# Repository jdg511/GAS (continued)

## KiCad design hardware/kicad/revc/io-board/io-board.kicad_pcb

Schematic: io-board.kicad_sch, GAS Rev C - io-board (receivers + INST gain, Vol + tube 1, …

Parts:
C21, C22, C31, C32, C41, C42, C51, C52, C61, C62, C71, C81, C83, C85, C91, C92, C111, C112, C901, C902, C921, C922: 100nF; C_0603_1608Metric; MPN CL10B104KB8NNNC
C82, C93, C94, C8004, C8104: 10uF 25V; CP_Elec_5x5.8; MPN UWT1E100MCL1GB
C84: 47uF 16V; CP_Elec_6.3x7.7; MPN EEE-FK1C470P
C95: 10uF; C_0805_2012Metric; MPN CL21A106KAYNNNE
C101, C121, C201, C301, C601, C611, C4005, C4105, C7005, C7105: 22pF; C_0603_1608Metric; MPN CL10C220JB8NNNC
C4001, C4101, C7001, C7101: 22nF C0G; C_1206_3216Metric; MPN GRM31C5C1H223JA01L
C4002, C4102, C7002, C7102: 10pF C0G; C_0603_1608Metric; MPN CL10C100JB8NNNC
C4003, C4103, C7003, C7103: 1uF; C_0805_2012Metric; MPN CL21B105KBFNNNE
C4004, C4104, C7004, C7104, C8001, C8003, C8006, C8101, C8103, C8106: 1uF film; C_Rect_L7.2mm_W4.5mm_P5.00mm_FKS2_FKP2_MKS2_MKP2; MPN MKS2C041001F00KSSD
C8002, C8102: 6.8nF C0G; C_0805_2012Metric; MPN C0805C682J5GACTU
C8005, C8105: 3.3nF C0G; C_0805_2012Metric; MPN C0805C332J5GACTU
D1F, D2F, D3F, D4F, D5F, D6F, D7F: 1N4148W; D_SOD-123; MPN 1N4148W-7-F
D4001, D4101, D7001, D7101: BAT54; SOT-23; MPN BAT54-7-F
H1, H2, H3, H4: M3; MountingHole_3.2mm_M3_Pad_Via
K1, K2, K3, K4, K5, K6, K7: G6K-2F-Y DC5; Relay_DPDT_Omron_G6K-2F-Y; MPN G6K-2F-Y DC5
P1: PWR (from power board); JST_VH_B4P-VH_1x04_P3.96mm_Vertical; MPN B4P-VH(LF)(SN)
P2: WET-SEND (to tank board); JST_XH_B3B-XH-A_1x03_P2.50mm_Vertical; MPN B3B-XH-A(LF)(SN)
P3: WET (from circuit board); JST_XH_B3B-XH-A_1x03_P2.50mm_Vertical; MPN B3B-XH-A(LF)(SN)
P4: CTL-A: Vol dual 10k lin push-pull, Output dual 10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; JST_XH_B12B-XH-A_1x12_P2.50mm_Vertical; MPN B12B-XH-A(LF)(SN)
P5: CTL-B: Wet/Dry dual 10k lin (control deck P3); JST_XH_B6B-XH-A_1x06_P2.50mm_Vertical; MPN B6B-XH-A(LF)(SN)
P6: AUDIO (from jack-board P2); JST_XH_B12B-XH-A_1x12_P2.50mm_Vertical; MPN B12B-XH-A(LF)(SN)
P7: MODE (from jack-board P3); JST_XH_B4B-XH-A_1x04_P2.50mm_Vertical; MPN B4B-XH-A(LF)(SN)
P8: CTL-D: switch lines (control deck P5); JST_XH_B5B-XH-A_1x05_P2.50mm_Vertical; MPN B5B-XH-A(LF)(SN)
Q4001, Q4101, Q7001, Q7101: MMBF5457; SOT-23; MPN MMBF5457
Q8001, Q8002, Q8101, Q8102: MMBT3904; SOT-23; MPN MMBT3904-7-F
R1, R2, R3, R4, R51, R52: 100R; R_0603_1608Metric; MPN RC0603FR-07100RL
R9, R20, R53, R58, R59, R81, R82, R102, R103, R104, R106, R122, R123, R124, R126, R625, R635, R4009, R4109, R7009, R7109, R8002, R8015, R8102, R8115: 10k; R_0603_1608Metric; MPN RC0603FR-0710KL
R11, R12, R13, R14, R15, R16, R17, R18: 10k 0.1%; R_0603_1608Metric; MPN ERA-3AEB103V
R19, R56, R57, R95, R8001, R8016, R8101, R8116: 100k; R_0603_1608Metric; MPN RC0603FR-07100KL
R54, R55, R203, R303, R603, R613, R4004, R4008, R4104, R4108, R7004, R7008, R7104, R7108: 1M; R_0603_1608Metric; MPN RC0603FR-071ML
R96: 825R; R_0603_1608Metric; MPN RC0603FR-07825RL
R101, R121: 30.1k; R_0603_1608Metric; MPN RC0603FR-0730K1L
R105, R125: 1.65k; R_0603_1608Metric; MPN RC0603FR-071K65L
R201, R202, R301, R302, R601, R602, R611, R612: 1.43k; R_0603_1608Metric; MPN RC0603FR-071K43L
R211, R212, R311, R312, R621, R622, R631, R632: 20k; R_0603_1608Metric; MPN RC0603FR-0720KL
R623, R633, R4006, R4106, R7006, R7106, R8005, R8007, R8105, R8107: 47k; R_0603_1608Metric; MPN RC0603FR-0747KL
R624, R634: 1.1k; R_0603_1608Metric; MPN RC0603FR-071K1L
R626, R636: 2.55k; R_0603_1608Metric; MPN RC0603FR-072K55L
R4001, R4101, R7001, R7101: 30.9k; R_0603_1608Metric; MPN RC0603FR-0730K9L
R4002, R4102, R7002, R7102: 1.00k; R_0603_1608Metric; MPN RC0603FR-071KL
R4003, R4103, R7003, R7103: 68k; R_0603_1608Metric; MPN RC0603FR-0768KL
R4005, R4105, R7005, R7105, R8011, R8111: 2.2k; R_0603_1608Metric; MPN RC0603FR-072K2L
R4007, R4107, R7007, R7107: 470k; R_0603_1608Metric; MPN RC0603FR-07470KL
R4010, R4110, R7010, R7110: 18k; R_0603_1608Metric; MPN RC0603FR-0718KL
R8003, R8012, R8013, R8103, R8112, R8113: 4.7k; R_0603_1608Metric; MPN RC0603FR-074K7L
R8004, R8104: 82k; R_0603_1608Metric; MPN RC0603FR-0782KL
R8006, R8008, R8106, R8108: 22k; R_0603_1608Metric; MPN RC0603FR-0722KL
R8009, R8010, R8109, R8110: 470R; R_0603_1608Metric; MPN RC0603FR-07470RL
R8014, R8114: 15k; R_0603_1608Metric; MPN RC0603FR-0715KL
RV4001, RV4101, RV7001, RV7101: 20k; Potentiometer_Bourns_3314J_Vertical; MPN 3314J-1-203E
U1, U11: OPA1644AIDR; SOIC-14_3.9x8.7mm_P1.27mm; MPN OPA1644AIDR
U2, U3, U4, U5, U6: OPA1679IDR; SOIC-14_3.9x8.7mm_P1.27mm; MPN OPA1679IDR
U7, U8: TL072HIDR; SOIC-8_3.9x4.9mm_P1.27mm; MPN TL072HIDR
U9, U10: DRV135UA; SOIC-8_3.9x4.9mm_P1.27mm; MPN DRV135UA
U81: L78L09; SOT-89-3; MPN L78L09ACUTR

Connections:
+5VAUX: P1.4, P8.4
+9VC: C71.1, C82.1, C83.1, C85.1, R81.1, R8005.1, R8007.1, R8012.1, R8013.1, R8105.1, R8107.1, R8112.1, R8113.1, U7.8 (V+), U8.8 (V+), U81.1 (OUT)
+15VA: C21.1, C31.1, C41.1, C51.1, C61.1, C81.1, C91.1, C93.1, C111.1, C901.1, C921.1, P1.1, R95.1, R4006.1, R4106.1, R7006.1, R7106.1, U1.4 (V+), U2.4 (V+), U3.4 (V+), U4.4 (V+), U5.4 (V+), U6.4 (V+), U9.6 (V+), U10.6 (V+), U11.4 (V+), U81.3 (IN)
-15VA: C22.2, C32.2, C42.2, C52.2, C62.2, C92.2, C94.2, C112.2, C902.2, C922.2, P1.3, U1.11 (V-), U2.11 (V-), U3.11 (V-), U4.11 (V-), U5.11 (V-), U6.11 (V-), U9.5 (V-), U10.5 (V-), U11.11 (V-)
AGND: C21.2, C22.1, C31.2, C32.1, C41.2, C42.1, C51.2, C52.1, C61.2, C62.1, C71.2, C81.2, C82.2, C83.2, C84.2, C85.2, C91.2, C92.1, C93.2, C94.1, C95.2, C111.2, C112.1, C901.2, C902.1, C921.2, C922.1, C4002.2, C4102.2, C7002.2, C7102.2, C8004.2, C8005.2, C8104.2, C8105.2, D1F.2 (A), D2F.2 (A), D3F.2 (A), D4F.2 (A), D5F.2 (A), D6F.2 (A), D7F.2 (A), H1.1, H2.1, H3.1, H4.1, K1.8, K2.8, K3.8, K4.8, K5.4, K5.5, K5.8, K6.4, K6.5, K6.8, K7.4, K7.5, K7.8, P1.2, P2.2, P3.2, P6.3, P6.6, P6.9, P6.12, P7.4, P8.5, R9.2, R14.2, R18.2, R19.2, R20.2, R53.2, R54.2, R55.2, R56.2, R57.2, R58.2, R59.2, R82.2, R96.2, R104.2, R106.2, R124.2, R126.2, R624.2, R625.2, R634.2, R635.2, R4002.2, R4005.2, R4008.2, R4009.2, R4102.2, R4105.2, R4108.2, R4109.2, R7002.2, R7005.2, R7008.2, R7009.2, R7102.2, R7105.2, R7108.2, R7109.2, R8006.2, R8008.2, R8011.2, R8016.2, R8106.2, R8108.2, R8111.2, R8116.2, U2.3 (+), U2.5 (+), U2.10 (+), U2.12 (+), U4.10 (+), U4.12 (+), U5.3 (+), U5.5 (+), U7.4 (V-), U8.4 (V-), U8.5 (+), U9.3 (GND), U10.3 (GND), U81.2 (GND)
BLEND_L: R601.1, U4.1, U4.2 (-)
BLEND_R: R611.1, U4.6 (-), U4.7
CTL_BYP: D7F.1 (K), K7.1, P7.3, R59.1
CTL_INST_L: D5F.1 (K), K1.5, K5.1, P7.1, R106.1
CTL_INST_R: K1.7, P7.2, R9.1
CTL_INST_R_K: D6F.1 (K), K1.6, K6.1, R126.1
CTL_MONO: D1F.1 (K), K1.1, P8.1, R20.1
CTL_TAPE: D4F.1 (K), K4.1, P8.3, R58.1
CTL_TUBE: D2F.1 (K), D3F.1 (K), K2.1, K3.1, P8.2, R53.1
DRVIN_L: U9.4 (VIN), U11.8, U11.9 (-)
DRVIN_R: U10.4 (VIN), U11.13 (-), U11.14
GN_L: C101.1, R101.1, R102.1, U11.2 (-)
GN_R: C121.1, R121.1, R122.1, U11.6 (-)
GRG_L: K5.3, R102.2
GRG_R: K6.3, R122.2
INB_L_N: R2.2, R11.1
INB_L_P: R1.2, R13.1
INB_R_N: R4.2, R15.1
INB_R_P: R3.2, R17.1
IN_L_COLD: P6.2, R2.1
IN_L_HOT: P6.1, R1.1
IN_R_COLD: P6.5, R4.1
IN_R_HOT: P6.4, R3.1
L_PROG: P5.1, R201.1, U1.8, U1.9 (-)
L_RX: R12.1, U1.1, U11.3 (+)
L_RXG: C101.2, K1.4, R101.2, U1.10 (+), U11.1
OCLEAN_L: K3.2, R622.2, U5.1
OCLEAN_R: K3.7, R632.2, U5.7
OCL_N_L: R621.2, R622.1, U5.2 (-)
OCL_N_R: R631.2, R632.1, U5.6 (-)
OFIN_L: K4.3, R103.1
OFIN_R: K4.6, R123.1
OTS_L: K3.3, K4.2, R623.1
OTS_R: K3.6, K4.7, R633.1
OUT_L_COLD: P6.8, U9.1 (-VO), U9.2 (-SENSE)
OUT_L_HI: P4.7, R601.2
OUT_L_HOT: P6.7, U9.7 (+SENSE), U9.8 (+VO)
OUT_L_LO: P4.9, R602.1
OUT_L_W: C601.1, P4.8, R603.1, U4.9 (-)
OUT_POT_L: C601.2, R602.2, R603.2, R621.1, R7001.1, U4.8
OUT_POT_R: C611.2, R612.2, R613.2, R631.1, R7101.1, U4.14
OUT_R_COLD: P6.11, U10.1 (-VO), U10.2 (-SENSE)
OUT_R_HI: P4.10, R611.2
OUT_R_HOT: P6.10, U10.7 (+SENSE), U10.8 (+VO)
OUT_R_LO: P4.12, R612.1
OUT_R_W: C611.1, P4.11, R613.1, U4.13 (-)
PADN_L: R103.2, R104.1, R105.1, U11.10 (+)
PADN_R: R123.2, R124.1, R125.1, U11.12 (+)
PSH_L: K5.6, R105.2
PSH_R: K6.6, R125.2
RX_L_M: R11.2, R12.2, U1.2 (-)
RX_L_P: R13.2, R14.1, U1.3 (+)
RX_R_M: R15.2, R16.2, U1.6 (-)
RX_R_P: R17.2, R18.1, U1.5 (+)
R_PROG: P5.4, R301.1, U1.13 (-), U1.14
R_RX: R16.1, U1.7, U11.5 (+)
R_RXG: C121.2, K1.2, R121.2, U11.7
R_SRC: K1.3, R19.1, U1.12 (+)
SPARE_U8_2: U8.6 (-), U8.7
TAPE_B1_L: C8003.2, Q8001.1 (B), R8005.2, R8006.1
TAPE_B1_R: C8103.2, Q8101.1 (B), R8105.2, R8106.1
TAPE_B2_L: C8004.1, Q8002.1 (B), R8007.2, R8008.1
TAPE_B2_R: C8104.1, Q8102.1 (B), R8107.2, R8108.1
TAPE_C1_L: Q8001.3 (C), R8012.2
TAPE_C1_R: Q8101.3 (C), R8112.2
TAPE_C2_L: Q8002.3 (C), R8013.2, R8014.1
TAPE_C2_R: Q8102.3 (C), R8113.2, R8114.1
TAPE_DIV_L: C8006.2, R8016.1, U5.10 (+)
TAPE_DIV_R: C8106.2, R8116.1, U5.12 (+)
TAPE_E1_L: Q8001.2 (E), R8009.1
TAPE_E1_R: Q8101.2 (E), R8109.1
TAPE_E2_L: Q8002.2 (E), R8010.1
TAPE_E2_R: Q8102.2 (E), R8110.1
TAPE_FB_L: R8002.1, R8003.1, R8004.2, U7.2 (-)
TAPE_FB_R: R8102.1, R8103.1, R8104.2, U7.6 (-)
TAPE_IN_L: C8001.2, R8001.1, U7.3 (+)
TAPE_IN_R: C8101.2, R8101.1, U7.5 (+)
TAPE_OUT_L: K4.4, R626.2, U5.8
TAPE_OUT_R: K4.5, R636.2, U5.14
TAPE_REC_L: C8003.1, R8004.1, U7.1
TAPE_REC_R: C8103.1, R8104.1, U7.7
TAPE_REP2_L: C8005.1, R8015.2
TAPE_REP2_R: C8105.1, R8115.2
TAPE_REP_L: C8006.1, R8014.2, R8015.1
TAPE_REP_R: C8106.1, R8114.2, R8115.1
TAPE_T_L: R8009.2, R8010.2, R8011.1
TAPE_T_R: R8109.2, R8110.2, R8111.1
TAPE_Z_L: C8002.1, R8003.2
TAPE_Z_R: C8102.1, R8103.2
TA_L_BIAS: C4003.2, D4001.3 (K), R4004.2, U3.1
TA_L_CC: C4001.2, R4003.1
TA_L_D: C4004.1, Q4001.1 (D), R4006.2
TA_L_G: C4002.1, D4001.1 (A), Q4001.3 (G), R4003.2, R4004.1
TA_L_MK_N: C4005.1, R4009.1, R4010.1, U3.6 (-)
TA_L_MK_T: R4010.2, RV4001.1
TA_L_OC: C4004.2, R4008.1, U3.5 (+)
TA_L_PAD: C4001.1, R4001.2, R4002.1
TA_L_S: Q4001.2 (S), R4005.1, R4007.1
TA_L_SV_N: C4003.1, R4007.2, U3.2 (-)
TA_OUT_L: C4005.2, K2.4, RV4001.2, RV4001.3, U3.7
TA_OUT_R: C4105.2, K2.5, RV4101.2, RV4101.3, U3.14
TA_R_BIAS: C4103.2, D4101.3 (K), R4104.2, U3.8
TA_R_CC: C4101.2, R4103.1
TA_R_D: C4104.1, Q4101.1 (D), R4106.2
TA_R_G: C4102.1, D4101.1 (A), Q4101.3 (G), R4103.2, R4104.1
TA_R_MK_N: C4105.1, R4109.1, R4110.1, U3.13 (-)
TA_R_MK_T: R4110.2, RV4101.1
TA_R_OC: C4104.2, R4108.1, U3.12 (+)
TA_R_PAD: C4101.1, R4101.2, R4102.1
TA_R_S: Q4101.2 (S), R4105.1, R4107.1
TA_R_SV_N: C4103.1, R4107.2, U3.9 (-)
TB_L_BIAS: C7003.2, D7001.3 (K), R7004.2, U6.1
TB_L_CC: C7001.2, R7003.1
TB_L_D: C7004.1, Q7001.1 (D), R7006.2
TB_L_G: C7002.1, D7001.1 (A), Q7001.3 (G), R7003.2, R7004.1
TB_L_MK_N: C7005.1, R7009.1, R7010.1, U6.6 (-)
TB_L_MK_T: R7010.2, RV7001.1
TB_L_OC: C7004.2, R7008.1, U6.5 (+)
TB_L_PAD: C7001.1, R7001.2, R7002.1
TB_L_S: Q7001.2 (S), R7005.1, R7007.1
TB_L_SV_N: C7003.1, R7007.2, U6.2 (-)
TB_OUT_L: C7005.2, K3.4, RV7001.2, RV7001.3, U6.7
TB_OUT_R: C7105.2, K3.5, RV7101.2, RV7101.3, U6.14
TB_R_BIAS: C7103.2, D7101.3 (K), R7104.2, U6.8
TB_R_CC: C7101.2, R7103.1
TB_R_D: C7104.1, Q7101.1 (D), R7106.2
TB_R_G: C7102.1, D7101.1 (A), Q7101.3 (G), R7103.2, R7104.1
TB_R_MK_N: C7105.1, R7109.1, R7110.1, U6.13 (-)
TB_R_MK_T: R7110.2, RV7101.1
TB_R_OC: C7104.2, R7108.1, U6.12 (+)
TB_R_PAD: C7101.1, R7101.2, R7102.1
TB_R_S: Q7101.2 (S), R7105.1, R7107.1
TB_R_SV_N: C7103.1, R7107.2, U6.9 (-)
TPM_N_L: R625.1, R626.1, U5.9 (-)
TPM_N_R: R635.1, R636.1, U5.13 (-)
TP_PAD_L: C8001.1, R623.2, R624.1
TP_PAD_R: C8101.1, R633.2, R634.1
TUBE_REF: C95.1, R95.2, R96.1, U3.3 (+), U3.10 (+), U6.3 (+), U6.10 (+)
VBIAS: C8002.2, C8102.2, R8001.2, R8002.2, R8101.2, R8102.2, U8.1, U8.2 (-)
VB_RAW: C84.1, R81.2, R82.1, U8.3 (+)
VCLEAN_L: K2.2, R212.2, U2.8
VCLEAN_R: K2.7, R312.2, U2.14
VCL_N_L: R211.2, R212.1, U2.9 (-)
VCL_N_R: R311.2, R312.1, U2.13 (-)
VOL_L_HI: P4.1, R201.2
VOL_L_LO: P4.3, R202.1
VOL_L_W: C201.1, P4.2, R203.1, U2.2 (-)
VOL_OUT_L: C201.2, R202.2, R203.2, R211.1, R4001.1, U2.1
VOL_OUT_R: C301.2, R302.2, R303.2, R311.1, R4101.1, U2.7
VOL_R_HI: P4.4, R301.2
VOL_R_LO: P4.6, R302.1
VOL_R_W: C301.1, P4.5, R303.1, U2.6 (-)
WD_L_W: P5.2, R54.1, U4.3 (+)
WD_R_W: P5.5, R55.1, U4.5 (+)
WET_L: P3.1, P5.3, R56.1
WET_R: P3.3, P5.6, R57.1
WET_SEND_L: P2.1, R51.2
WET_SEND_R: P2.3, R52.2
WSEND_RAW_L: K2.3, K7.2
WSEND_RAW_R: K2.6, K7.7
WSEND_SW_L: K7.3, R51.1
WSEND_SW_R: K7.6, R52.1

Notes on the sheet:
Jacks and connectors
Mechanical
Balanced receivers, INST gain, Mono > Stereo, dry
Tube reference and +9VC / VBIAS
Vol (+/-18 dB) and clean inverters
Tube 1: 6GY8 section emulation after Vol
Wet send select
Wet/Dry buffers and Output (+/-18 dB)
Tube 2: 6GY8 section emulation after Output
Output clean inverters, tube select, tape make-ups
Tape (Output pull): record EQ, MMBT3904 pair, repro EQ, +9VC
Balanced line drivers (DRV135, cross-coupled: TS plug safe)
Power flags

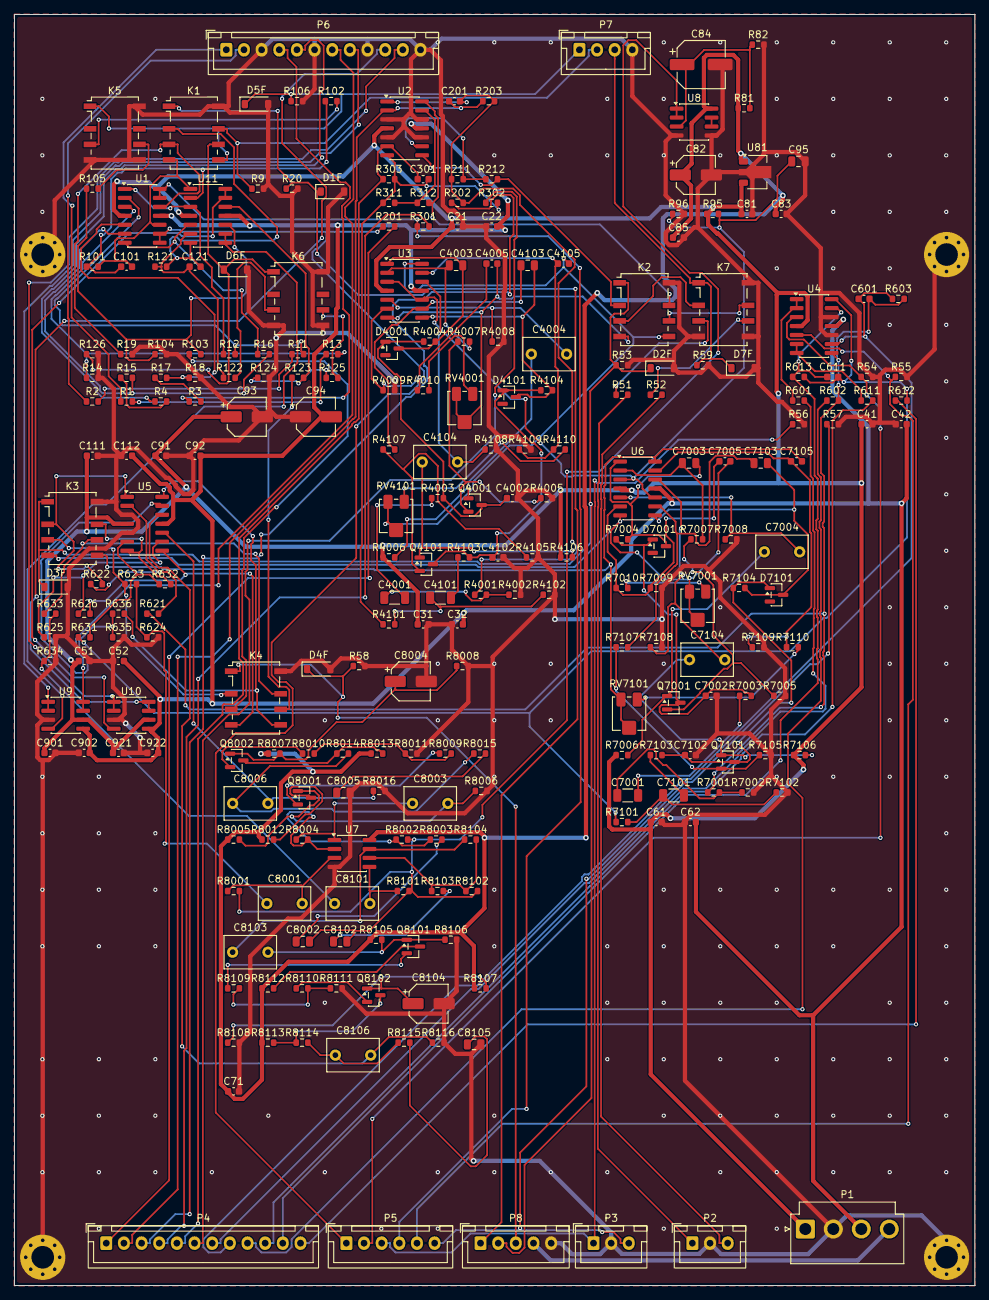
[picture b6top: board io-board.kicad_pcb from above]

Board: 2 copper layers, 136.0 x 180.0 mm, 259 parts (0 on the bottom side), 167 nets.

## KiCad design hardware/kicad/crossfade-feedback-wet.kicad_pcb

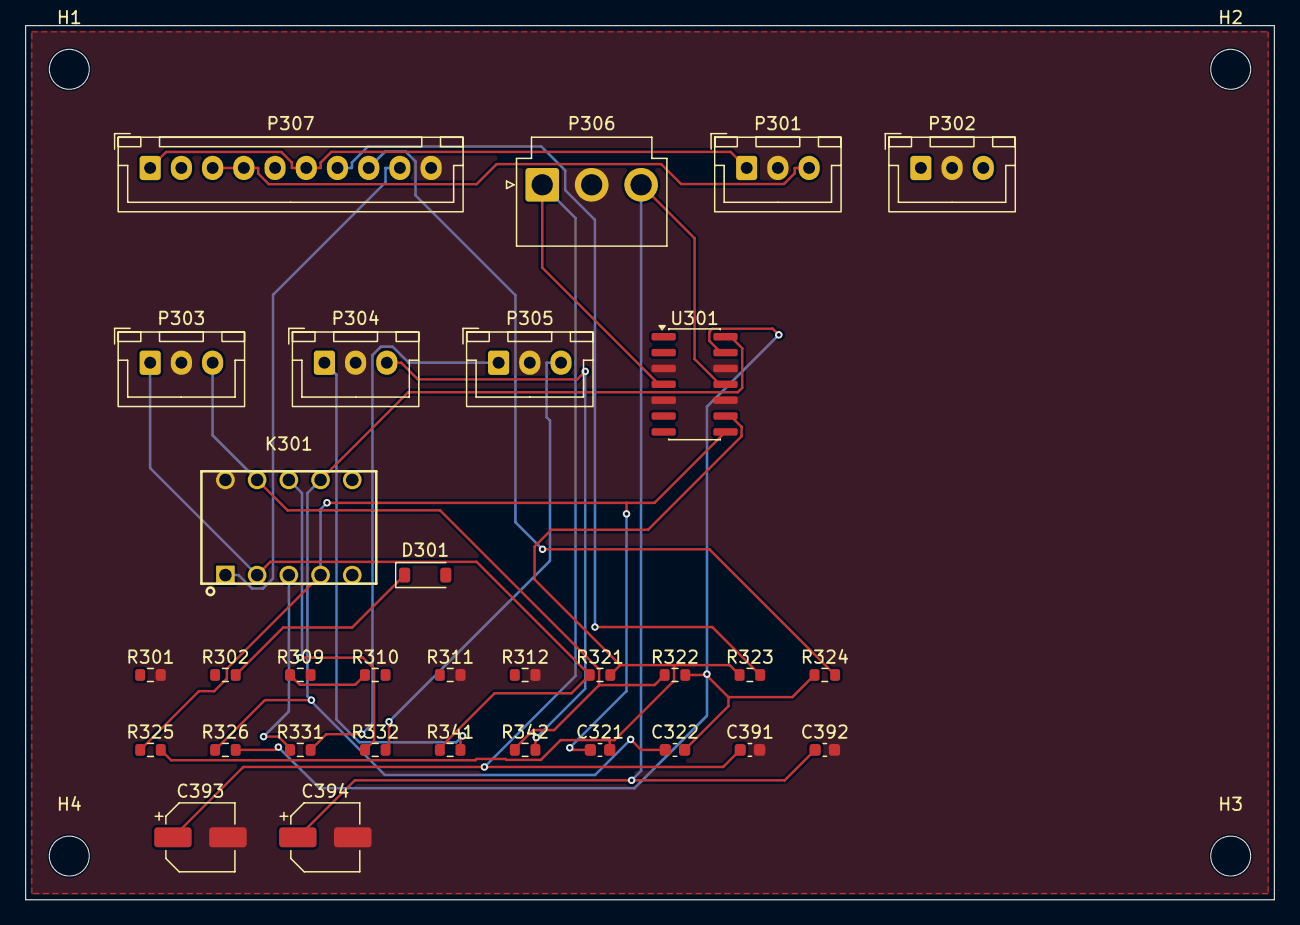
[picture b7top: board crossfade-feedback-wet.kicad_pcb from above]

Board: 2 copper layers, 100.0 x 70.0 mm, 36 parts (0 on the bottom side), 22 nets.

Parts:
C321, C322: 47pF DNP; C_0603_1608Metric
C391, C392: 100nF; C_0603_1608Metric
C393, C394: 10uF; CP_Elec_5x5.8
D301: 1N4148; D_SOD-123
H1, H2, H3, H4: M3 NPTH; MountingHole_3.2mm_M3
K301: TQ2-5V; Relay_DPDT_Panasonic_TQ2
P301: JTR-XFADE; JST_XH_B3B-XH-A_1x03_P2.50mm_Vertical
P302: JXF-FILT; JST_XH_B3B-XH-A_1x03_P2.50mm_Vertical
P303: JFILT-WET; JST_XH_B3B-XH-A_1x03_P2.50mm_Vertical
P304: JIO-WETRET; JST_XH_B3B-XH-A_1x03_P2.50mm_Vertical
P305: JFB-INJ; JST_XH_B3B-XH-A_1x03_P2.50mm_Vertical
P306: JXFD-PWR; JST_VH_B3P-VH_1x03_P3.96mm_Vertical
P307: JXFD-CTRL; JST_XH_B10B-XH-A_1x10_P2.50mm_Vertical
R301, R302, R309, R310, R321, R322, R323, R324: 20k; R_0603_1608Metric
R311, R312, R331, R332, R341, R342: 100R; R_0603_1608Metric
R325, R326: 10k; R_0603_1608Metric
U301: OPA1679IDR; SOIC-14_3.9x8.7mm_P1.27mm

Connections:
+15VA: C391.1, C393.1, P306.1, U301.4
-15VA: C392.1, C394.1, P306.3, U301.11
AGND: C391.2, C392.2, C393.2, C394.2, K301.A2, P301.2, P302.2, P303.2, P304.2, P305.2, P306.2, P307.10, R301.2, R311.2, R312.2, U301.3, U301.5, U301.10, U301.12
CTL_FB_INV: K301.A1, P307.9
FB_INV_L: C321.1, K301.14, R325.1, U301.8
FB_INV_R: C322.1, K301.24, R326.1, U301.14
FB_L_SUM: C321.2, R321.2, R323.1, R325.2, U301.9
FB_L_WIPER: P307.7, R323.2
FB_RET_L: P305.1, R331.2
FB_RET_R: P305.3, R332.2
FB_R_SUM: C322.2, R322.2, R324.1, R326.2, U301.13
FB_R_WIPER: P307.8, R324.2
FB_SEL_L: K301.11, R331.1
FB_SEL_R: K301.21, R332.1
FILTCLIP_OUT_L: K301.12, P303.1, R321.1, R341.1
FILTCLIP_OUT_R: K301.22, P303.3, R322.1, R342.1
SL_BIAS_MID: D301.1, R302.2
SL_TANK: R309.1, R310.1
TANK_MIX_L: P301.1, P307.1, P307.6
TANK_MIX_R: P301.3, P307.3, P307.4
WET_SUM_L: P304.1, R341.2
WET_SUM_R: P304.3, R342.2

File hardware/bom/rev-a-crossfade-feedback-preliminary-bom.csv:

RefDes,Qty,MPN,Description,Notes
U301,1,OPA1679IDR,"Quad audio op amp","U301A/U301B crossfade summers, U301C/U301D feedback drivers"
P301,1,B3B-XH-A,"3-position signal header","Input from ext-routing board: TANK_MIX_L, AGND, TANK_MIX_R"
P302,1,B3B-XH-A,"3-position signal header","Output to filter/clipper board: XFADE_OUT_L, AGND, XFADE_OUT_R"
P303,1,B3B-XH-A,"3-position signal header","Return from filter/clipper board: FILTCLIP_OUT_L, AGND, FILTCLIP_OUT_R"
P304,1,B3B-XH-A,"3-position signal header","Direct wet return to I/O board: WET_SUM_L, AGND, WET_SUM_R"
P305,1,B3B-XH-A,"3-position signal header","Feedback reinjection output: FB_RET_L, AGND, FB_RET_R"
P306,1,B3P-VH-B,"3-position power header","Board power input: +15VA, AGND, -15VA"
P307,1,B10B-XH-A,"10-position grouped control header","Current rev-A grouped landing for crossfade, feedback amount, feedback phase invert, and AGND; may grow if raw passive feedback-pot wiring is expanded later"
R301,1,RC0603FR-0720KL,"20k 1% resistor, 0603","Left crossfade entry: XFD_L_WIPER to U301A-"
R302,1,RC0603FR-0720KL,"20k 1% resistor, 0603","Right crossfade entry: XFD_R_WIPER to U301B-"
R309,1,RC0603FR-0720KL,"20k 1% resistor, 0603","Left crossfade unity-gain feedback"
R310,1,RC0603FR-0720KL,"20k 1% resistor, 0603","Right crossfade unity-gain feedback"
R311,1,RC0603FR-07100RL,"100R 1% resistor, 0603","Left filter-send isolator"
R312,1,RC0603FR-07100RL,"100R 1% resistor, 0603","Right filter-send isolator"
R321,1,RC0603FR-0720KL,"20k 1% resistor, 0603","Left feedback-driver input from FILTCLIP_OUT_L"
R322,1,RC0603FR-0720KL,"20k 1% resistor, 0603","Right feedback-driver input from FILTCLIP_OUT_R"
R323,1,RC0603FR-0720KL,"20k 1% resistor, 0603","Left feedback amount return-path start value; trim-friendly"
R324,1,RC0603FR-0720KL,"20k 1% resistor, 0603","Right feedback amount return-path start value; trim-friendly"
R325,1,RC0603FR-0710KL,"10k 1% resistor, 0603","Left minimum loop-floor feedback"
R326,1,RC0603FR-0710KL,"10k 1% resistor, 0603","Right minimum loop-floor feedback"
R331,1,RC0603FR-07100RL,"100R 1% resistor, 0603","Left feedback-send isolator after phase selection"
R332,1,RC0603FR-07100RL,"100R 1% resistor, 0603","Right feedback-send isolator after phase selection"
R341,1,RC0603FR-07100RL,"100R 1% resistor, 0603","Left final wet-return isolator"
R342,1,RC0603FR-07100RL,"100R 1% resistor, 0603","Right final wet-return isolator"
C321,1,C0603C470J5GACTU,"47pF NP0 capacitor, 0603, DNP default","Left feedback-driver stability footprint"
C322,1,C0603C470J5GACTU,"47pF NP0 capacitor, 0603, DNP default","Right feedback-driver stability footprint"
C391,1,CC0603KRX7R9BB104,"100nF X7R capacitor, 0603","Local +15VA decoupling near U301 power unit"
C392,1,CC0603KRX7R9BB104,"100nF X7R capacitor, 0603","Local -15VA decoupling near U301 power unit"
C393,1,UWX1E100MCL1GB,"10uF 25V electrolytic or polymer support cap","Local positive-rail bulk footprint; power-path only"
C394,1,UWX1E100MCL1GB,"10uF 25V electrolytic or polymer support cap","Local negative-rail bulk footprint; power-path only"

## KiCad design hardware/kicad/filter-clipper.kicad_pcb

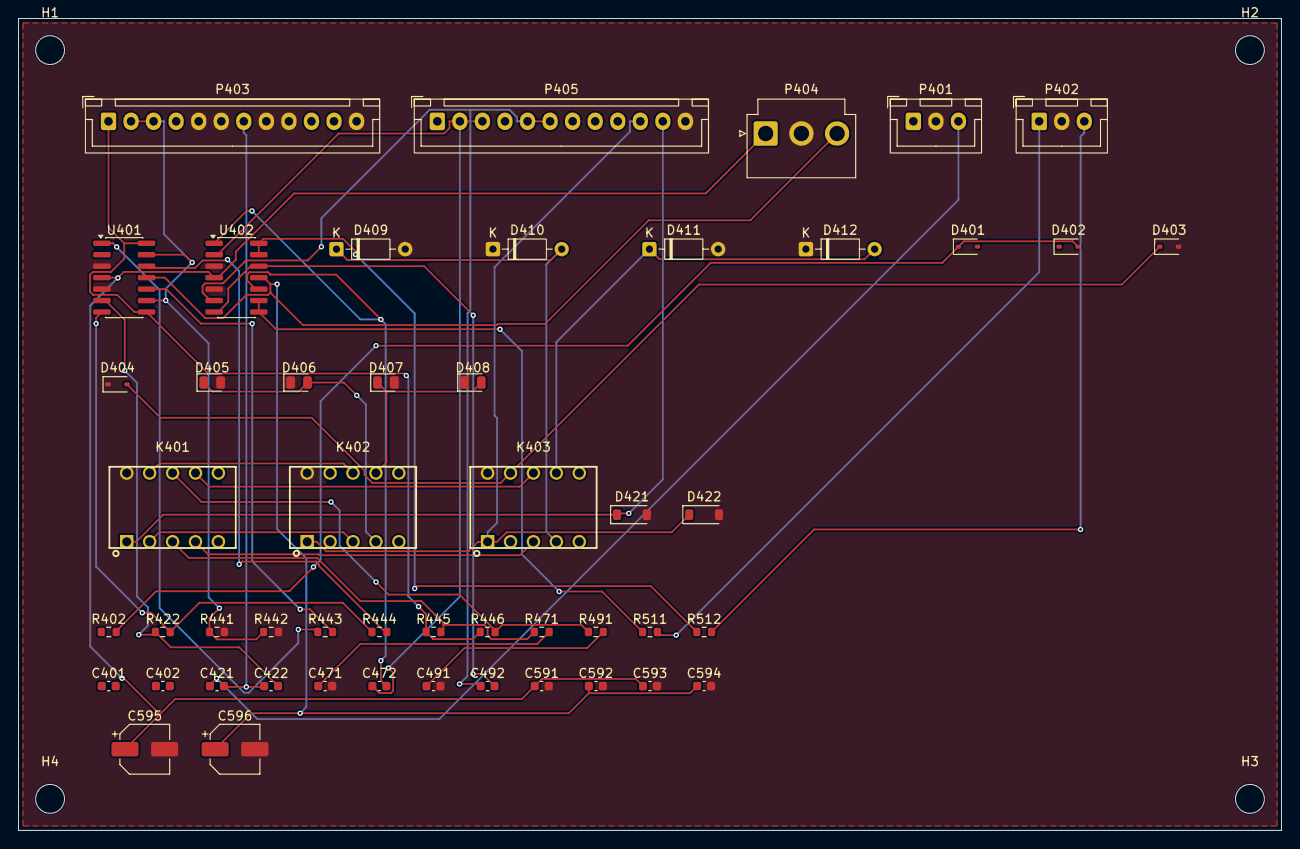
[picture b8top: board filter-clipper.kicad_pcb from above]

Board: 2 copper layers, 140.0 x 90.0 mm, 54 parts (0 on the bottom side), 36 nets.

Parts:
C401, C402, C421, C422, C471, C472, C491, C492: 22nF; C_0603_1608Metric
C591, C592, C593, C594: 100nF; C_0603_1608Metric
C595, C596: 10uF; CP_Elec_5x5.8
D401, D402, D403, D404: 1N4148WS; D_SOD-323
D405, D406, D407, D408: Clip LED; LED_0805_2012Metric
D409, D410, D411, D412: Ge clip or adapter; D_DO-35_SOD27_P7.62mm_Horizontal
D421, D422: 1N4148; D_SOD-123
H1, H2, H3, H4: M3 NPTH; MountingHole_3.2mm_M3
K401, K402, K403: TQ2-5V; Relay_DPDT_Panasonic_TQ2
P401: JXF-FILT; JST_XH_B3B-XH-A_1x03_P2.50mm_Vertical
P402: JFILT-WET; JST_XH_B3B-XH-A_1x03_P2.50mm_Vertical
P403: JFILT-CTL-A; JST_XH_B12B-XH-A_1x12_P2.50mm_Vertical
P404: JFILT-PWR; JST_VH_B3P-VH_1x03_P3.96mm_Vertical
P405: JFILT-CTL-B; JST_XH_B12B-XH-A_1x12_P2.50mm_Vertical
R402, R422: 30k; R_0603_1608Metric
R441, R442, R445, R446: 10k; R_0603_1608Metric
R443, R444: 1k; R_0603_1608Metric
R471, R491: 15k; R_0603_1608Metric
R511, R512: 100R; R_0603_1608Metric
U401, U402: OPA1679IDR; SOIC-14_3.9x8.7mm_P1.27mm

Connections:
+15VA: C591.1, C593.1, C595.1, P404.1, U401.4, U402.4
-15VA: C592.1, C594.1, C596.1, P404.3, U401.11, U402.11
AGND: C471.2, C491.2, C591.2, C592.2, C593.2, C594.2, C595.2, C596.2, D403.2, D404.1, D405.2, D406.1, D407.2, D408.1, D409.2, D410.1, D411.2, D412.1, D421.2, D422.2, K401.A2, K402.A2, K403.A2, P401.2, P402.2, P403.5, P403.6, P403.8, P403.9, P403.12, P404.2, P405.12, R441.2, R442.2, U401.3, U401.5, U402.3, U402.5
BUF_OUT_L: R511.1, U402.8, U402.9
BUF_OUT_R: R512.1, U402.13, U402.14
CLIP_NODE_L: K401.11, R445.2, R471.1
CLIP_NODE_R: K401.21, R446.2, R491.1
CLIP_W0_L: K401.12, K402.11
CLIP_W0_R: K401.22, K402.21
CLIP_W1_L: K401.14, K403.11
CLIP_W1_R: K401.24, K403.21
CTL_CLIP_MODE_A: D422.1, K402.A1, K403.A1, P405.10
CTL_CLIP_MODE_B: D421.1, K401.A1, P405.11
DRV_HI: P403.1, R445.1, R446.1, U401.8, U401.14
DRV_PRE_L: R443.2, U401.10
DRV_PRE_R: R444.2, U401.12
DRV_WIPER: P403.2, P403.3, R441.1, R442.1, U401.9, U401.13
FILTCLIP_OUT_L: P402.1, R511.2
FILTCLIP_OUT_R: P402.3, R512.2
GE_CLIP_L: D409.1, D410.2, K403.14
GE_CLIP_R: D411.1, D412.2, K403.24
HPF_F_R_HI: C421.2, C422.1, P403.7
HPF_OUT_L: R443.1, U401.1
HPF_OUT_R: R422.2, R444.1, U401.7
HPF_R_A: C422.2, R422.1, U401.6
LED_CLIP_L: D405.1, D406.2, K402.14
LED_CLIP_R: D407.1, D408.2, K402.24
LPF_L_A: C472.1, P405.2, P405.3, U402.2
LPF_N1_L: C471.1, R471.2
LPF_N1_R: C491.1, R491.2
LPF_OUT_L: C472.2, U402.1, U402.10
LPF_OUT_R: C492.2, U402.7, U402.12
LPF_R_A: C492.1, P405.5, P405.6, U402.6
SIL_CLIP_R: D403.1, D404.2, K403.22
SR_BIAS_MID: D401.1, D402.2, R402.2
XFADE_OUT_R: C421.1, P401.3

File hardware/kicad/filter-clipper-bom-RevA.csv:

"Refs","Value","Footprint","DNP","Qty"
"C401,C402,C421,C422,C471,C472,C491,C492","22nF","Capacitor_SMD:C_0603_1608Metric","","8"
"C591-C594","100nF","Capacitor_SMD:C_0603_1608Metric","","4"
"C595,C596","10uF","Capacitor_SMD:CP_Elec_5x5.8","","2"
"D401,D403","1N4148WS","Diode_SMD:D_SOD-323","DNP","2"
"D402,D404","1N4148WS","Diode_SMD:D_SOD-323","","2"
"D405,D407","Clip LED","LED_SMD:LED_0805_2012Metric","DNP","2"
"D406,D408","Clip LED","LED_SMD:LED_0805_2012Metric","","2"
"D409,D411","Ge clip or adapter","Diode_THT:D_DO-35_SOD27_P7.62mm_Horizontal","DNP","2"
"D410,D412","Ge clip or adapter","Diode_THT:D_DO-35_SOD27_P7.62mm_Horizontal","","2"
"D421,D422","1N4148","Diode_SMD:D_SOD-123","","2"
"K401-K403","TQ2-5V","GAS_Parts:Relay_DPDT_Panasonic_TQ2","","3"
"P401","JXF-FILT","Connector_JST:JST_XH_B3B-XH-A_1x03_P2.50mm_Vertical","","1"
"P402","JFILT-WET","Connector_JST:JST_XH_B3B-XH-A_1x03_P2.50mm_Vertical","","1"
"P403","JFILT-CTL-A","Connector_JST:JST_XH_B12B-XH-A_1x12_P2.50mm_Vertical","","1"
"P404","JFILT-PWR","Connector_JST:JST_VH_B3P-VH_1x03_P3.96mm_Vertical","","1"
"P405","JFILT-CTL-B","Connector_JST:JST_XH_B12B-XH-A_1x12_P2.50mm_Vertical","","1"
"R402,R422","30k","Resistor_SMD:R_0603_1608Metric","","2"
"R441,R442,R445,R446","10k","Resistor_SMD:R_0603_1608Metric","","4"
"R443,R444","1k","Resistor_SMD:R_0603_1608Metric","","2"
"R471,R491","15k","Resistor_SMD:R_0603_1608Metric","","2"
"R511,R512","100R","Resistor_SMD:R_0603_1608Metric","","2"
"U401,U402","OPA1679IDR","Package_SO:SOIC-14_3.9x8.7mm_P1.27mm","","2"

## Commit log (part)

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2026-06-10 Define GAS release v2.5
2026-06-10 Add macOS plugin build workflow
2026-06-10 Place plugin IRs in bundle resources
2026-06-10 Limit builds and refine mono standalone approval pass
2026-06-23 UI refactor: contemporary font, art under title, mono LR swap, inverted buttons, new layout
2026-06-23 Add GitHub Actions workflow: build Windows Standalone on push
2026-06-23 Major UI overhaul: Art Nouveau, Input mode, aligned layout, combobox-style buttons
2026-06-27 Fix mono input routing: Mono L/R selects input channel; enable Mono-Source-To-Stereo for mono input only
2026-06-28 Ext tanks: additive pot law in both Series and Parallel (true single-pot consistency)
